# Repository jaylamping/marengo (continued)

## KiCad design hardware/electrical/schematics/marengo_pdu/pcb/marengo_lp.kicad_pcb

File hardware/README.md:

# Hardware

Physical robot design for Marengo: CAD, electrical, prints, and BOM. Mechanics and wiring are defined here first; software reads the exports.

**Status for the software project: [`STATUS.md`](STATUS.md).** Hardware threads update it in the same commit whenever a milestone lands (built/tested parts, joint names, limits, CAN IDs, URDF, new software requirements).

## Layout

| Path | Purpose |
|------|---------|
| [`../cad/`](../cad/) | SolidWorks parts, assemblies, vendor STEP, MCP manifests |
| [`electrical/`](electrical/) | PDB (KiCad stub), harness and CAN documentation |
| [`prints/`](prints/) | STL sources and slicer notes |
| [`bom/`](bom/) | Master BOM and sourcing |
| [`docs/`](docs/) | Kinematics (joint SSOT), torso design, assembly, homing sensors, CAD standards, hardware ADRs, [RobStride manuals](docs/robstride/README.md) |

## Active design

| Target | Status |
|--------|--------|
| Humanoid rev-a (G1/R1-class biped, 1524 mm, 23 DOF) | Torso frame 140×150×340 mm committed; pelvis/shell draft — [`docs/kinematics.md`](docs/kinematics.md) |
| Right arm (5 DOF, live bench) | First subsystem wired and commissioning: [`config/robot.yaml`](../config/robot.yaml) + [`assets/urdf/marengo.urdf`](../assets/urdf/marengo.urdf) (geometry and inertials from CAD, 2026-10-03). It is the first slice of the humanoid arm, not a separate robot |
| Electrical | Pi 5 + 2-CH MCP2515 CAN HAT + BNO085 IMU on the bench. PDB/PDU KiCad project is an empty stub; 48 V pack and full harness are draft |

Full-body runtime templates (not loaded until remaining joints are commissioned): [`config/robot_humanoid.yaml`](../config/robot_humanoid.yaml), [`config/motors_humanoid.yaml`](../config/motors_humanoid.yaml).

## Revision

When you cut a build, record the mechanical/electrical revision here (e.g. `rev-a`, date, known deltas from prior rev).

| Rev | Date | Scope |
|-----|------|-------|
| rev-a (in progress) | 2026 | 2020 upper-torso cage committed; right 5-DOF arm built and on the bench; everything else draft |

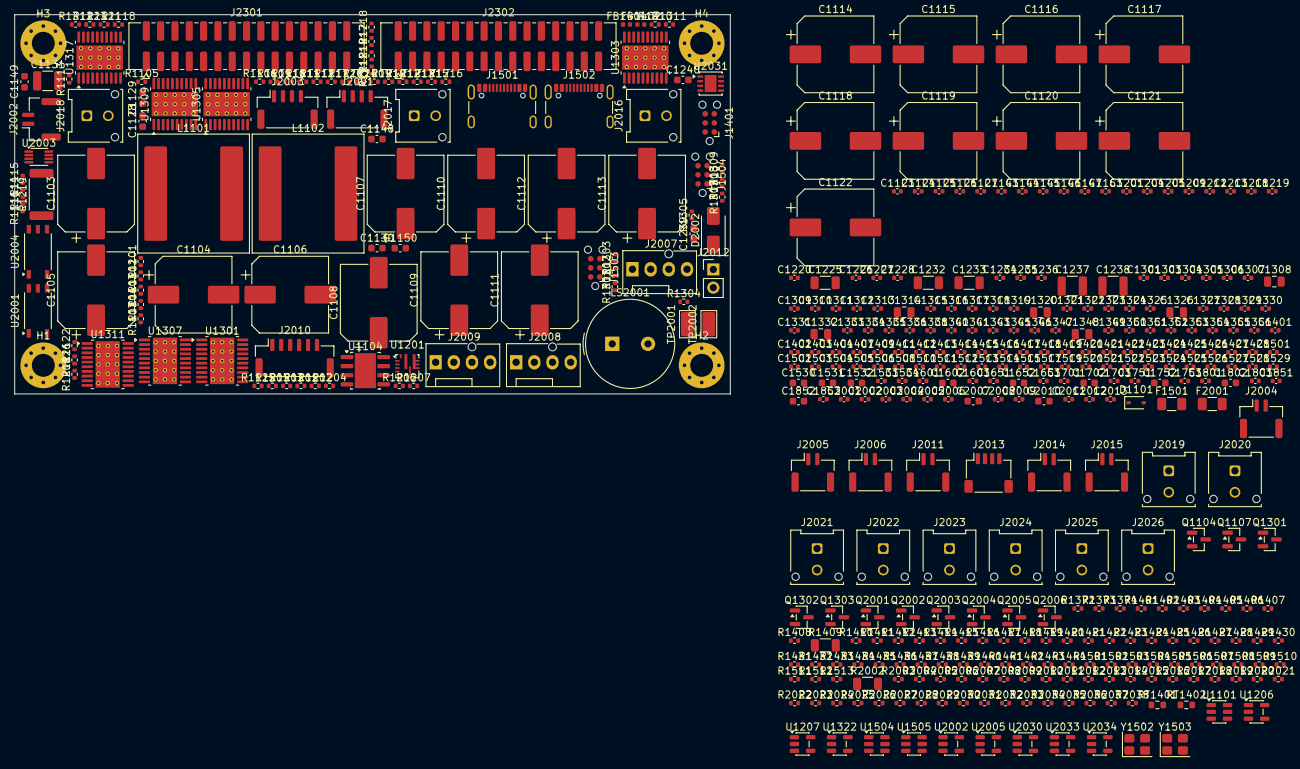
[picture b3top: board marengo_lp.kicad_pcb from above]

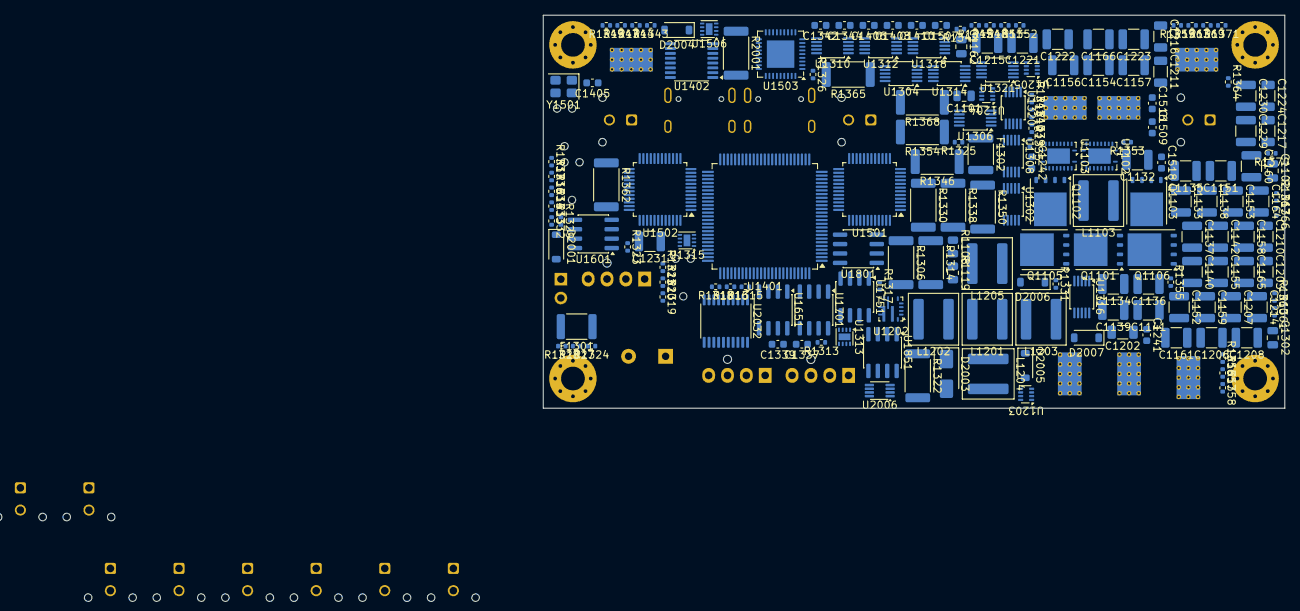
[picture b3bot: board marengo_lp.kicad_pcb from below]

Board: 6 copper layers, 100.0 x 53.0 mm, 611 parts (177 on the bottom side), 354 nets, no tracks yet.

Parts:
C1101, C1102, C1162: 100nF 100V; C_0805_2012Metric
C1103, C1104, C1105, C1106, C1107, C1108, C1109, C1110, C1111, C1112, C1113, C1114, C1115, C1116, C1117, C1118, C1119, C1120, C1121, C1122: 68uF 80V B40950B0686M100; CP_Elec_10x10.5
C1123, C1412, C1413, C1414, C1415, C1416, C1417, C1418, C1419, C1421, C1422, C1423, C1424, C1425, C1426, C1427, C1508, C1517: 10nF; C_0402_1005Metric
C1124: 33pF; C_0402_1005Metric
C1125, C1338, C1343, C1420, C1533: 1nF; C_0402_1005Metric
C1126, C1146, C1220, C1228, C1236: 33nF; C_0402_1005Metric
C1127, C1147: 100nF 25V; C_0402_1005Metric
C1128, C1148: 2.2uF 25V; C_0603_1608Metric
C1129: 18pF C0G 100V; C_0603_1608Metric
C1130, C1150: 100nF 100V; C_0603_1608Metric
C1131, C1132, C1133, C1134, C1135, C1151, C1152, C1153, C1161: 4.7uF 100V; C_1210_3225Metric
C1136, C1137, C1138, C1139, C1140, C1141, C1142, C1164, C1165, C1166, C1206, C1207, C1208, C1214, C1215, C1221, C1222, C1223, C1229, C1230, C1231, C1237, C1238: 22uF 25V; C_1210_3225Metric
C1143: 6.8nF; C_0402_1005Metric
C1144: 10pF; C_0402_1005Metric
C1145: 680pF; C_0402_1005Metric
C1149: 22pF C0G 100V; C_0603_1608Metric
C1154, C1155, C1156, C1157, C1158, C1159, C1160: 10uF 50V; C_1210_3225Metric
C1163, C1204, C1205, C1212, C1213, C1218, C1219, C1226, C1227, C1234, C1235, C1305, C1306, C1311, C1312, C1317, C1318, C1323, C1324, C1329, C1330, C1335, C1336, C1340, C1341, C1345, C1346, C1351, C1352, C1353, C1354, C1355, C1356, C1401, C1402, C1403, C1404, C1407, C1409, C1411, C1428, C1503, C1504, C1505, C1506, C1512, C1513, C1514, C1515, C1521, C1522, C1523, C1524, C1525, C1526, C1527, C1528, C1529, C1534, C1601, C1603, C1651, C1653, C1701, C1703, C1751, C1753, C1801, C1803, C1851, C1853, C2001, C2002, C2003, C2004, C2005, C2006, C2008, C2009, C2011, C2012, C2013: 100nF; C_0402_1005Metric
C1201, C1209: 220pF C0G; C_0402_1005Metric
C1202, C1203, C1210, C1211, C1216, C1217, C1224, C1225, C1232, C1233: 10uF 50V; C_1206_3216Metric
C1239, C1240, C1241, C1242, C1337, C1342, C1531: 1uF 10V; C_0603_1608Metric
C1301: 22nF; C_0402_1005Metric
C1302, C1308, C1314, C1320, C1326, C1332, C1348: 1uF 50V; C_0805_2012Metric
C1303, C1304, C1309, C1310, C1315, C1316, C1321, C1322, C1327, C1328, C1333, C1334, C1349, C1350: 100nF 50V; C_0402_1005Metric
C1307, C1313, C1319, C1325, C1331, C1347: 47nF; C_0402_1005Metric
C1339, C1344, C1532: 10uF 10V; C_0603_1608Metric
C1405, C1406, C1410, C1507, C1516, C1530, C1602, C1652, C1702, C1752, C1802, C1852: 4.7uF; C_0603_1608Metric
C1408, C1509, C1518: 1uF; C_0603_1608Metric
C1501, C1502, C1510, C1511, C1519, C1520: 12pF C0G; C_0402_1005Metric
C2007, C2010: 2.2uF; C_0603_1608Metric
D1101: BAT54 30V; D_SOD-323
D2001, D2007: 1N4148W; D_SOD-123
D2002, D2003: SMAJ15A; D_SMA
D2004, D2005, D2006: BAT54; D_SOD-123
F1301: 2.5A MF-MSMF250/16X-2; Fuse_1812_4532Metric
F1302: 1.1A MF-MSMF110/16-2; Fuse_1812_4532Metric
F1501, F2001: 0.5A polyfuse; Fuse_1206_3216Metric
FB1401, FB1402: BLM15; L_0402_1005Metric
H1, H2, H3, H4: M3 standoff; MountingHole_3.2mm_M3_Pad_Via
J1401, J1503, J1504: SWD Tag-Connect; Tag-Connect_TC2030-IDC-NL_2x03_P1.27mm_Vertical
J1501: USB4105-GF-A, up to Pi; USB_C_Receptacle_GCT_USB4105-xx-A_16P_TopMnt_Horizontal
J1502: USB4105-GF-A, service; USB_C_Receptacle_GCT_USB4105-xx-A_16P_TopMnt_Horizontal
J2001: E-stop loop; JST_GH_SM04B-GHS-TB_1x04-1MP_P1.25mm_Horizontal
J2002: tether, shorting dummy; JST_GH_SM02B-GHS-TB_1x02-1MP_P1.25mm_Horizontal
J2003: wireless contact, shorting plug; JST_GH_SM04B-GHS-TB_1x04-1MP_P1.25mm_Horizontal
J2004: brake thermostat NC; JST_GH_SM02B-GHS-TB_1x02-1MP_P1.25mm_Horizontal
J2005: wireless receiver power; JST_GH_SM02B-GHS-TB_1x02-1MP_P1.25mm_Horizontal
J2006: E-stop reset, NO button; JST_GH_SM02B-GHS-TB_1x02-1MP_P1.25mm_Horizontal
J2007: fan 1; FanPinHeader_1x04_P2.54mm_Vertical
J2008: fan 2; FanPinHeader_1x04_P2.54mm_Vertical
J2009: fan 3; FanPinHeader_1x04_P2.54mm_Vertical
J2010: shell: button + RGB; JST_GH_SM06B-GHS-TB_1x06-1MP_P1.25mm_Horizontal
J2011: charge LED; JST_GH_SM02B-GHS-TB_1x02-1MP_P1.25mm_Horizontal
J2012: bench jumper; PinHeader_1x02_P2.54mm_Vertical
J2013: Qwiic; JST_SH_SM04B-SRSS-TB_1x04-1MP_P1.00mm_Horizontal
J2014: intake NTC; JST_GH_SM02B-GHS-TB_1x02-1MP_P1.25mm_Horizontal
J2015: exhaust NTC; JST_GH_SM02B-GHS-TB_1x02-1MP_P1.25mm_Horizontal
J2016: OUT_24V; Molex_Micro-Fit_3.0_43045-0212_2x01_P3.00mm_Vertical
J2017: OUT_12V_JETSON; Molex_Micro-Fit_3.0_43045-0212_2x01_P3.00mm_Vertical
J2018: OUT_12V_THIRD; Molex_Micro-Fit_3.0_43045-0212_2x01_P3.00mm_Vertical
J2019: OUT_12V_AUX; Molex_Micro-Fit_3.0_43045-0212_2x01_P3.00mm_Vertical
J2020: OUT_12V_PI_STUB; Molex_Micro-Fit_3.0_43045-0212_2x01_P3.00mm_Vertical
J2021: OUT_7V4_SERVO; Molex_Micro-Fit_3.0_43045-0212_2x01_P3.00mm_Vertical
J2022: OUT_5V_PERIPH; Molex_Micro-Fit_3.0_43045-0212_2x01_P3.00mm_Vertical
J2023: OUT_3V3_PERIPH; Molex_Micro-Fit_3.0_43045-0212_2x01_P3.00mm_Vertical
J2024: OUT_SPARE; Molex_Micro-Fit_3.0_43045-0212_2x01_P3.00mm_Vertical
J2025: 5V_CLEAN; Molex_Micro-Fit_3.0_43045-0212_2x01_P3.00mm_Vertical
J2026: 3V3_CLEAN; Molex_Micro-Fit_3.0_43045-0212_2x01_P3.00mm_Vertical
J2301: 2x15 2 mm box, power and logic; Molex_8783230xx_2x15_P2.0mm_Header_Vertical_Polarized
J2302: 2x15 2 mm box, CAN and analog; Molex_8783230xx_2x15_P2.0mm_Header_Vertical_Polarized
L1101: XAL1510-682MED; L_Coilcraft_XAL1510-682
L1102: XAL1510-333MED; L_Coilcraft_XAL1510-333
L1103: XAL6060-223MEC 22uH; L_Coilcraft_XAL6060-XXX
L1201: XAL6060-562MEC 5.6uH; L_Coilcraft_XAL6060-XXX
L1202: XAL6030-332MEC 3.3uH; L_Coilcraft_XAL6030-XXX
L1203: XAL6060-472MEC 4.7uH; L_Coilcraft_XAL6060-XXX
L1204, L1205: XAL6060-682MEC 6.8uH; L_Coilcraft_XAL6060-XXX
LS2001: PS1240P02BT; Buzzer_TDK_PS1240P02BT_D12.2mm_H6.5mm
Q1101: CSD19532Q5B; TDSON-8-1
Q1102, Q1105, Q1106: CSD19534Q5A; TDSON-8-1
Q1103: BSC040N10NS5ATMA1; TDSON-8-1
Q1104, Q1107: BSS123; SOT-23
Q1301, Q1302, Q1303, Q2001, Q2002, Q2003, Q2004, Q2005, Q2006: 2N7002; SOT-23
R1101, R1102, R1112, R1359: 33.2k; R_0402_1005Metric
R1103: 2.37k; R_0402_1005Metric
R1104, R1309, R1317: 6.04k; R_0402_1005Metric
R1105, R1116: 100R; R_0402_1005Metric
R1106, R1117: 2.2R; R_0402_1005Metric
R1107: 348R; R_0402_1005Metric
R1108: 1.21M; R_0805_2012Metric
R1109: 49.9k; R_0402_1005Metric
R1110, R1121, R1203, R1209: 20k; R_0402_1005Metric
R1111, R1122, R1123, R1126, R1206, R1212, R1349, R1353, R1372, R1438, R1439, R1502, R1503, R1507, R1508, R1513, R2005, R2011, R2022, R2023, R2024, R2025, R2026, R2027, R2028, R2029, R2030, R2031, R2038: 100k; R_0402_1005Metric
R1113: 80.6k; R_0402_1005Metric
R1114: 2.8k; R_0402_1005Metric
R1115: 17.8k; R_0402_1005Metric
R1118: 301R; R_0402_1005Metric
R1119: 499k; R_0805_2012Metric
R1120: 18.2k; R_0402_1005Metric
R1124: 43.2k; R_0402_1005Metric
R1125, R1344: 64.9k; R_0402_1005Metric
R1201: 113k; R_0402_1005Metric
R1202, R1208, R1214, R1216, R1218, R1371, R1373, R1374, R1412, R1414, R1416, R1418, R1420, R1422, R1436, R1437, R1440, R1441, R1504, R1505, R1506, R2015, R2017, R2018, R2019, R2020, R2021, R2036, R2037: 10k; R_0402_1005Metric
R1204, R1210: 169k; R_0402_1005Metric
R1205, R1211: 36.1k; R_0402_1005Metric
R1207: 73.2k; R_0402_1005Metric
R1213: 31.6k; R_0402_1005Metric
R1215: 52.3k; R_0402_1005Metric
R1217: 60.4k; R_0402_1005Metric
R1219: 4.7R 1W; R_2512_6332Metric
R1301, R1333, R1357: 4.99k; R_0402_1005Metric
R1302: 475k; R_0402_1005Metric
R1303: 7.87k; R_0402_1005Metric
R1304: 22.1k; R_0402_1005Metric
R1305, R1313, R1321, R1329, R1337, R1345, R1361: 33k; R_0402_1005Metric
R1306, R1314, R1322, R1330, R1338, R1354, R1362, R1365: 10mR 3W; R_2512_6332Metric
R1307, R1308, R1315, R1316, R1323, R1324, R1331, R1332, R1339, R1340, R1347, R1348, R1351, R1352, R1355, R1356, R1363, R1364, R1366, R1367, R1369, R1370: 10R; R_0402_1005Metric
R1310, R1318, R1326, R1334: 442k; R_0402_1005Metric
R1311, R1319, R1327, R1335: 21.5k; R_0402_1005Metric
R1312, R1320, R1328, R1336: 41.2k; R_0402_1005Metric
R1325: 4.53k; R_0402_1005Metric
R1341: 3.01k; R_0402_1005Metric
R1342: 383k; R_0402_1005Metric
R1343: 54.9k; R_0402_1005Metric
R1346, R1350: 5mR 3W; R_2512_6332Metric
R1358: 365k; R_0402_1005Metric
R1360: 97.6k; R_0402_1005Metric
R1368: 2mR 3W; R_2512_6332Metric
R1401, R1402, R1403, R1404, R1405, R1406, R1407, R1408, R1411, R1413, R1415, R1417, R1419, R1421, R1423, R1442, R1443, R1444, R2004, R2006, R2010, R2012, R2016: 1k; R_0402_1005Metric
R1409: 1M 0.1%; R_1206_3216Metric
R1410: 56k 0.1%; R_0402_1005Metric
R1424, R1425, R1426, R1427, R1428, R1429, R1430, R1431, R1432, R1433, R1434, R1435: 2.2k; R_0402_1005Metric
R1501: 12.0k 1%; R_0402_1005Metric
R1509, R1510: 5.1k; R_0402_1005Metric
R1511, R1512: 56k; R_0402_1005Metric
R2001: 680R 1W; R_2512_6332Metric
R2002: 620R 0.25W; R_1206_3216Metric
R2003, R2009: 10k Cat 0 filter; R_0402_1005Metric
R2007, R2013: 160k; R_0402_1005Metric
R2008, R2014: 1M; R_0402_1005Metric
R2032, R2033, R2034, R2035: 330R; R_0402_1005Metric
RT1401, RT1402: 10k B3435; R_0603_1608Metric
TP2001, TP2002: TP; TestPoint_Keystone_5015_Micro_Mini
U1101: LM5050MK-1; TSOT-23-6
U1102, U1103: LM5145RGYR; Texas_RGY_R-PVQFN-N20_EP2.05x3.05mm
U1104: LMR38010SDDAR; SOIC-8-1EP_3.9x4.9mm_P1.27mm_EP2.95x4.9mm_Mask2.71x3.4mm
U1201, U1202: TPS56637RPAR; TPS56637_RPA_VQFN-HR-10
U1203, U1204: TPS62933DRLR; SOT-583-8
U1205: TPS62933FDRLR; SOT-583-8
U1206: TPS7A2050PDBVR; SOT-23-5
U1207: TPS7A2033PDBVR; SOT-23-5
U1301, U1303, U1305, U1307, U1309, U1311, U1317: TPS26631PWPR; HTSSOP-20-1EP_4.4x6.5mm_P0.65mm_EP3.4x6.5mm_Mask2.96x2.96mm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
U1302, U1304, U1306, U1308, U1310, U1312, U1314, U1316, U1318, U1320, U1321: INA238AIDGSR; TSSOP-10_3x3mm_P0.5mm
U1313, U1315, U1506: TPS22965DSGR; Texas_DSG0008A_WSON-8-1EP_2x2mm_P0.5mm_EP0.9x1.6mm
U1322, U2002, U2005, U2030: SN74LVC1G14DBV; SOT-23-5
U1401: STM32G0B1VET6; LQFP-100_14x14mm_P0.5mm
U1402: TCA9546APWR; TSSOP-16_4.4x5mm_P0.65mm
U1501, U1502: STM32G474CET6; LQFP-48_7x7mm_P0.5mm
U1503: USB2514B-I/M2; QFN-36-1EP_6x6mm_P0.5mm_EP3.7x3.7mm
U1504, U1505: USBLC6-2SC6; SOT-23-6
U1601, U1651, U1701, U1751, U1801, U1851: TCAN1462VDRQ1; SOIC-8_3.9x4.9mm_P1.27mm
U2001, U2004: ISOM8710; ISOM8710_DFF
U2003, U2006: SN74LVC1G74DCUR; VSSOP-8_2.3x2mm_P0.5mm
U2031: TPS3431SDRBR; VSON-8-1EP_3x3mm_P0.65mm_EP1.65x2.4mm
U2032: SN74LVC244APWR; TSSOP-20_4.4x6.5mm_P0.65mm
U2033, U2034: SN74LVC1G08DBV; SOT-23-5
Y1501, Y1502, Y1503: ABM8G-24.000MHZ-4Y-T; Crystal_SMD_3225-4Pin_3.2x2.5mm

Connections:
+3V3_AON: C1164.1, C1165.1, C1166.1, C1306.1, C1312.1, C1318.1, C1324.1, C1330.1, C1336.1, C1341.1, C1346.1, C1352.1, C1354.1, C1356.1, C1401.1, C1402.1, C1403.1, C1404.1, C1405.1, C1406.1, C1428.1, C1504.1, C1505.1, C1506.1, C1507.1, C1508.1, C1509.1, C1513.1, C1514.1, C1515.1, C1516.1, C1517.1, C1518.1, C1524.1, C1525.1, C1526.1, C1527.1, C1528.1, C1529.1, C1530.1, C1603.1, C1653.1, C1703.1, C1753.1, C1803.1, C1853.1, C2001.1, C2002.1, C2003.1, C2004.1, C2006.1, C2009.1, C2012.1, C2013.1, FB1401.1, FB1402.1, J1401.1, J1503.1, J1504.1, J2010.1, J2013.2, L1103.2, R1110.2, R1121.2, R1122.1, R1123.1, R1126.2, R1206.2, R1212.2, R1371.2, R1372.2, R1373.2, R1374.2, R1424.2, R1425.2, R1426.2, R1427.2, R1428.2, R1429.2, R1430.2, R1431.2, R1432.2, R1433.2, R1434.2, R1435.2, R1436.2, R1437.2, R1440.2, R1441.2, R1502.2, R1503.2, R1506.2, R2005.2, R2008.2, R2011.2, R2014.2, R2015.2, R2016.2, R2019.2, R2020.2, R2021.2, R2036.2, R2037.2, U1302.6, U1304.2, U1304.6, U1306.6, U1308.6, U1310.1, U1310.6, U1312.6, U1314.2, U1314.6, U1316.6, U1318.6, U1320.1, U1320.6, U1321.1, U1321.2, U1321.6, U1322.5, U1401.11, U1401.13, U1401.64, U1402.16, U1501.1, U1501.20, U1501.21, U1501.24, U1501.36, U1501.48, U1502.1, U1502.20, U1502.21, U1502.24, U1502.36, U1502.48, U1503.5, U1503.10, U1503.15, U1503.23, U1503.29, U1503.36, U1601.5, U1651.5, U1701.5, U1751.5, U1801.5, U1851.5, U2001.5, U2002.5, U2003.7, U2003.8, U2004.5, U2005.5, U2006.7, U2006.8, U2030.5, U2031.1, U2031.5, U2032.20, U2033.5, U2034.5
+3V3_CLEAN: C1242.1, J2026.1, U1207.5
+3V3_HP: C1409.1, C1410.1, FB1402.2, J2301.28
+5V_CLEAN: C1240.1, J2025.1, U1206.5
+12V: C1136.1, C1137.1, C1138.1, C1139.1, C1140.1, C1141.1, C1142.1, C1202.1, C1203.1, C1204.1, C1210.1, C1211.1, C1212.1, C1216.1, C1217.1, C1218.1, C1224.1, C1225.1, C1226.1, C1232.1, C1233.1, C1234.1, C1308.1, C1309.1, C1314.1, C1315.1, C1320.1, C1321.1, C1326.1, C1327.1, D1101.2, F2001.1, J2007.2, J2008.2, J2009.2, R1102.1, R1105.1, R1204.1, R1210.1, R1310.1, R1318.1, R1326.1, R1334.1, R1368.2, R1370.1, R2001.1, U1201.8, U1202.8, U1203.3, U1204.3, U1205.3, U1303.1, U1303.2, U1303.3, U1303.6, U1305.1, U1305.2, U1305.3, U1305.6, U1307.1, U1307.2, U1307.3, U1307.6, U1309.1, U1309.2, U1309.3, U1309.6, U1321.8
+24V: C1154.1, C1155.1, C1156.1, C1157.1, C1158.1, C1159.1, C1160.1, C1302.1, C1303.1, L1102.2, R1113.1, R1116.1, R1302.1, U1301.1, U1301.2, U1301.3, U1301.6
/LP_logic_board/can_bridges_usb_hub/CRFILT: C1521.1, U1503.14
/LP_logic_board/can_bridges_usb_hub/HSE_I_A: C1501.1, U1501.5, Y1501.1
/LP_logic_board/can_bridges_usb_hub/HSE_I_B: C1510.1, U1502.5, Y1502.1
/LP_logic_board/can_bridges_usb_hub/HSE_O_A: C1502.1, U1501.6, Y1501.3
/LP_logic_board/can_bridges_usb_hub/HSE_O_B: C1511.1, U1502.6, Y1502.3
/LP_logic_board/can_bridges_usb_hub/HUB_XI: C1519.1, U1503.33, Y1503.1
/LP_logic_board/can_bridges_usb_hub/HUB_XO: C1520.1, U1503.32, Y1503.3
/LP_logic_board/can_bridges_usb_hub/NRST_A: C1503.1, J1503.3, U1501.7
/LP_logic_board/can_bridges_usb_hub/NRST_B: C1512.1, J1504.3, U1502.7
/LP_logic_board/can_bridges_usb_hub/PLLFILT: C1522.1, U1503.34
/LP_logic_board/can_bridges_usb_hub/RBIAS: R1501.1, U1503.35
/LP_logic_board/can_bridges_usb_hub/STRAP_CF0: R1504.1, U1503.24
/LP_logic_board/can_bridges_usb_hub/STRAP_CF1: R1505.1, U1503.25
/LP_logic_board/can_bridges_usb_hub/STRAP_NR0: R1503.1, U1503.28
/LP_logic_board/can_bridges_usb_hub/STRAP_NR1: R1502.1, U1503.22
/LP_logic_board/can_bridges_usb_hub/SVC_CC1: J1502.A5, R1511.2
/LP_logic_board/can_bridges_usb_hub/SVC_CC2: J1502.B5, R1512.2
/LP_logic_board/can_bridges_usb_hub/SVC_CT: C1533.1, U1506.6
/LP_logic_board/can_bridges_usb_hub/SVC_PWR_EN: R1513.1, U1503.20, U1506.3
/LP_logic_board/can_bridges_usb_hub/SVC_SW: C1532.1, F1501.1, U1506.7, U1506.8
/LP_logic_board/can_bridges_usb_hub/SVC_VBUS: F1501.2, J1502.A4, J1502.A9, J1502.B4, J1502.B9, U1505.5
/LP_logic_board/can_bridges_usb_hub/SWCLK_A: J1503.4, U1501.38
/LP_logic_board/can_bridges_usb_hub/SWCLK_B: J1504.4, U1502.38
/LP_logic_board/can_bridges_usb_hub/SWDIO_A: J1503.2, U1501.37
/LP_logic_board/can_bridges_usb_hub/SWDIO_B: J1504.2, U1502.37
/LP_logic_board/can_bridges_usb_hub/UP_CC1: J1501.A5, R1509.1
/LP_logic_board/can_bridges_usb_hub/UP_CC2: J1501.B5, R1510.1
/LP_logic_board/can_bridges_usb_hub/UP_VBUS: C1534.1, J1501.A4, J1501.A9, J1501.B4, J1501.B9, R1507.1, U1504.5
/LP_logic_board/can_bridges_usb_hub/USB_SVC_DM: J1502.A7, J1502.B7, U1503.8, U1505.1, U1505.6
/LP_logic_board/can_bridges_usb_hub/USB_SVC_DP: J1502.A6, J1502.B6, U1503.9, U1505.3, U1505.4
/LP_logic_board/can_bridges_usb_hub/USB_UP_DM: J1501.A7, J1501.B7, U1503.30, U1504.1, U1504.6
/LP_logic_board/can_bridges_usb_hub/USB_UP_DP: J1501.A6, J1501.B6, U1503.31, U1504.3, U1504.4
/LP_logic_board/can_bridges_usb_hub/VBUS_DET: R1507.2, R1508.1, U1503.27
/LP_logic_board/front_end_12v_24v/BOOT_AON: C1163.1, U1104.7
/LP_logic_board/front_end_12v_24v/BST_12: C1127.1, U1102.17
/LP_logic_board/front_end_12v_24v/BST_24: C1147.1, U1103.17
/LP_logic_board/front_end_12v_24v/BSW_12: C1127.2, R1106.1
/LP_logic_board/front_end_12v_24v/BSW_24: C1147.2, R1117.1
/LP_logic_board/front_end_12v_24v/CC_12: C1123.1, R1104.2
/LP_logic_board/front_end_12v_24v/CC_24: C1143.1, R1115.2
/LP_logic_board/front_end_12v_24v/COMP_12: C1124.1, R1104.1, U1102.4
/LP_logic_board/front_end_12v_24v/COMP_24: C1144.1, R1115.1, U1103.4
/LP_logic_board/front_end_12v_24v/EN_12: Q1104.3, R1108.2, R1109.1, U1102.1
/LP_logic_board/front_end_12v_24v/EN_24: Q1107.3, R1119.2, R1120.1, U1103.1
/LP_logic_board/front_end_12v_24v/FB_12: C1123.2, C1124.2, C1125.2, R1102.2, R1103.1, U1102.5
/LP_logic_board/front_end_12v_24v/FB_24: C1143.2, C1144.2, C1145.2, R1113.2, R1114.1, U1103.5
/LP_logic_board/front_end_12v_24v/FB_AON: R1123.2, R1124.1, U1104.5
/LP_logic_board/front_end_12v_24v/FF_12: C1125.1, R1105.2
/LP_logic_board/front_end_12v_24v/FF_24: C1145.1, R1116.2
/LP_logic_board/front_end_12v_24v/HO_12: Q1102.4, U1102.18
/LP_logic_board/front_end_12v_24v/HO_24: Q1105.4, U1103.18
/LP_logic_board/front_end_12v_24v/ILIM_12: C1129.1, R1107.1, U1102.11
/LP_logic_board/front_end_12v_24v/ILIM_24: C1149.1, R1118.1, U1103.11
/LP_logic_board/front_end_12v_24v/LO_12: Q1103.4, U1102.13
/LP_logic_board/front_end_12v_24v/LO_24: Q1106.4, U1103.13
/LP_logic_board/front_end_12v_24v/OR_GATE: Q1101.4, U1101.5
/LP_logic_board/front_end_12v_24v/PG_AON: R1126.1, U1104.6
/LP_logic_board/front_end_12v_24v/RT_12: R1101.1, U1102.2
/LP_logic_board/front_end_12v_24v/RT_24: R1112.1, U1103.2
/LP_logic_board/front_end_12v_24v/RT_AON: R1125.1, U1104.4
/LP_logic_board/front_end_12v_24v/SS_12: C1126.1, U1102.3
/LP_logic_board/front_end_12v_24v/SS_24: C1146.1, U1103.3
/LP_logic_board/front_end_12v_24v/SW12: L1101.1, Q1102.1, Q1102.2, Q1102.3, Q1103.5, R1106.2, R1107.2, U1102.19
/LP_logic_board/front_end_12v_24v/SW24: L1102.1, Q1105.1, Q1105.2, Q1105.3, Q1106.5, R1117.2, R1118.2, U1103.19
/LP_logic_board/front_end_12v_24v/SW_AON: C1163.2, L1103.1, U1104.8
/LP_logic_board/front_end_12v_24v/SYNC_24: U1102.7, U1103.8
/LP_logic_board/front_end_12v_24v/VCC_12: C1128.1, D1101.1, U1102.8, U1102.14
/LP_logic_board/front_end_12v_24v/VCC_24: C1148.1, U1103.14
/LP_logic_board/front_end_12v_24v/VSYS_OR: C1102.1, C1103.1, C1104.1, C1105.1, C1106.1, C1107.1, C1108.1, C1109.1, C1110.1, C1111.1, C1112.1, C1113.1, C1114.1, C1115.1, C1116.1, C1117.1, C1118.1, C1119.1, C1120.1, C1121.1, C1122.1, C1130.1, C1131.1, C1132.1, C1133.1, C1134.1, C1135.1, C1161.1, C1162.1, Q1101.5, Q1102.5, R1108.1, U1101.6, U1102.20, U1104.2, U1104.3
/LP_logic_board/io_fans_estop_loop/ARM_A: R2004.1, R2017.1, U2003.5
/LP_logic_board/io_fans_estop_loop/ARM_B: R2010.1, U2006.5
/LP_logic_board/io_fans_estop_loop/BUZ_D: D2007.2, LS2001.2, Q2006.3
/LP_logic_board/io_fans_estop_loop/CLR_A: U2003.6, U2033.4
/LP_logic_board/io_fans_estop_loop/CLR_B: U2006.6, U2034.4
/LP_logic_board/io_fans_estop_loop/ESTOP_RST: U2003.1, U2006.1, U2030.4
/LP_logic_board/io_fans_estop_loop/ESTOP_RST_N: C2011.1, J2006.1, R2015.1, U2030.2
/LP_logic_board/io_fans_estop_loop/FAN1_DRV: J2007.4, Q2003.3
/LP_logic_board/io_fans_estop_loop/FAN2_DRV: J2008.4, Q2004.3
/LP_logic_board/io_fans_estop_loop/FAN3_DRV: J2009.4, Q2005.3
/LP_logic_board/io_fans_estop_loop/INV_A: C2005.1, C2007.1, D2004.2, R2003.2, R2007.2, R2008.1, U2002.2
/LP_logic_board/io_fans_estop_loop/INV_B: C2008.1, C2010.1, D2005.2, R2009.2, R2013.2, R2014.1, U2005.2
/LP_logic_board/io_fans_estop_loop/LB: J2010.4, R2034.2
/LP_logic_board/io_fans_estop_loop/LC: J2011.1, R2035.2
/LP_logic_board/io_fans_estop_loop/LG: J2010.3, R2033.2
/LP_logic_board/io_fans_estop_loop/LOOP_M: U2001.2, U2004.1
/LP_logic_board/io_fans_estop_loop/LOOP_N: D2001.2, R2002.1, U2004.2
/LP_logic_board/io_fans_estop_loop/LOOP_OUT: D2002.1, J2001.1, R2001.2, TP2001.1
/LP_logic_board/io_fans_estop_loop/LOOP_RET: D2001.1, D2003.1, J2004.2, TP2002.1, U2001.1
/LP_logic_board/io_fans_estop_loop/LOOP_TH: J2003.3, J2004.1
/LP_logic_board/io_fans_estop_loop/LR: J2010.2, R2032.2
/LP_logic_board/io_fans_estop_loop/OPTO_A: D2004.1, R2003.1, R2006.1, R2007.1, U2001.4
/LP_logic_board/io_fans_estop_loop/OPTO_B: D2005.1, R2009.1, R2012.1, R2013.1, U2004.4
/LP_logic_board/io_fans_estop_loop/OUT_A: U2002.4, U2003.2, U2033.1
/LP_logic_board/io_fans_estop_loop/OUT_B: U2005.4, U2006.2, U2034.1
/LP_logic_board/io_fans_estop_loop/PORT_OE_N: U2003.3, U2032.1, U2032.19
/LP_logic_board/io_fans_estop_loop/TETH_A: J2001.3, J2002.1
/LP_logic_board/io_fans_estop_loop/TETH_B: J2002.2, J2003.1
/LP_logic_board/io_fans_estop_loop/WL_12V: F2001.2, J2005.1
/LP_logic_board/pol_rails/BOOT_5V: C1213.1, U1202.7
/LP_logic_board/pol_rails/BOOT_7V4: C1205.1, U1201.7
/LP_logic_board/pol_rails/BST_3V3: C1219.1, U1203.6
/LP_logic_board/pol_rails/BST_5V6: C1235.1, U1205.6
/LP_logic_board/pol_rails/BST_SPARE: C1227.1, U1204.6
/LP_logic_board/pol_rails/ENB_5V: R1210.2, R1211.1, U1202.1
/LP_logic_board/pol_rails/ENB_7V4: R1204.2, R1205.1, U1201.1
/LP_logic_board/pol_rails/FB_3V3: R1213.2, R1214.1, U1203.8
/LP_logic_board/pol_rails/FB_5V: C1209.2, R1207.2, R1208.1, U1202.2
/LP_logic_board/pol_rails/FB_5V6: R1217.2, R1218.1, U1205.8
/LP_logic_board/pol_rails/FB_7V4: C1201.2, R1201.2, R1202.1, U1201.2
/LP_logic_board/pol_rails/FB_SPARE: R1215.2, R1216.1, U1204.8
/LP_logic_board/pol_rails/FF_5V: C1209.1, R1209.2
/LP_logic_board/pol_rails/FF_7V4: C1201.1, R1203.2
/LP_logic_board/pol_rails/IN_CLEAN3: C1241.1, R1219.2, U1207.1
/LP_logic_board/pol_rails/PG_5V: R1212.1, U1202.4
/LP_logic_board/pol_rails/PG_7V4: R1206.1, U1201.4
/LP_logic_board/pol_rails/SS_3V3: C1220.1, U1203.7
/LP_logic_board/pol_rails/SS_5V6: C1236.1, U1205.7
/LP_logic_board/pol_rails/SS_SPARE: C1228.1, U1204.7
/LP_logic_board/pol_rails/SW_3V3: C1219.2, L1203.1, U1203.5
/LP_logic_board/pol_rails/SW_5V: C1213.2, L1202.1, U1202.6
/LP_logic_board/pol_rails/SW_5V6: C1235.2, L1205.1, U1205.5
/LP_logic_board/pol_rails/SW_7V4: C1205.2, L1201.1, U1201.6
/LP_logic_board/pol_rails/SW_SPARE: C1227.2, L1204.1, U1204.5
/LP_logic_board/rail_switches_meters/CT_3V3: C1343.1, U1315.6
/LP_logic_board/rail_switches_meters/CT_5V: C1338.1, U1313.6
/LP_logic_board/rail_switches_meters/DV_7V4: C1331.1, U1311.10
/LP_logic_board/rail_switches_meters/DV_12V_AUX: C1319.1, U1307.10
/LP_logic_board/rail_switches_meters/DV_12V_JETSON: C1307.1, U1303.10
/LP_logic_board/rail_switches_meters/DV_12V_PI: C1325.1, U1309.10
/LP_logic_board/rail_switches_meters/DV_12V_THIRD: C1313.1, U1305.10
/LP_logic_board/rail_switches_meters/DV_24V: C1301.1, U1301.10
/LP_logic_board/rail_switches_meters/DV_SPARE: C1347.1, U1317.10
/LP_logic_board/rail_switches_meters/IL_7V4: R1341.1, U1311.11
/LP_logic_board/rail_switches_meters/IL_12V_AUX: R1325.1, U1307.11
/LP_logic_board/rail_switches_meters/IL_12V_JETSON: R1309.1, U1303.11
/LP_logic_board/rail_switches_meters/IL_12V_PI: R1333.1, U1309.11
/LP_logic_board/rail_switches_meters/IL_12V_THIRD: R1317.1, U1305.11
/LP_logic_board/rail_switches_meters/IL_24V: R1301.1, U1301.11
/LP_logic_board/rail_switches_meters/IL_SPARE: R1357.1, U1317.11
/LP_logic_board/rail_switches_meters/OV_7V4: R1343.2, R1344.1, U1311.8
/LP_logic_board/rail_switches_meters/OV_12V_AUX: R1327.2, R1328.1, U1307.8
/LP_logic_board/rail_switches_meters/OV_12V_JETSON: R1311.2, R1312.1, U1303.8
/LP_logic_board/rail_switches_meters/OV_12V_PI: R1335.2, R1336.1, U1309.8
/LP_logic_board/rail_switches_meters/OV_12V_THIRD: R1319.2, R1320.1, U1305.8
/LP_logic_board/rail_switches_meters/OV_24V: R1303.2, R1304.1, U1301.8
/LP_logic_board/rail_switches_meters/OV_SPARE: R1359.2, R1360.1, U1317.8
/LP_logic_board/rail_switches_meters/RAW_5V6_M: R1365.2, R1367.1, U1320.8
/LP_logic_board/rail_switches_meters/SHED_12V: Q1301.1, Q1302.1, Q1303.1, U1322.4
/LP_logic_board/rail_switches_meters/SHED_N: R1371.1, U1321.3, U1322.2
/LP_logic_board/rail_switches_meters/SN_3V3: C1345.2, R1356.2, U1316.9
/LP_logic_board/rail_switches_meters/SN_5V: C1340.2, R1352.2, U1314.9
/LP_logic_board/rail_switches_meters/SN_7V4: C1335.2, R1348.2, U1312.9
/LP_logic_board/rail_switches_meters/SN_12V_AUX: C1323.2, R1332.2, U1308.9
/LP_logic_board/rail_switches_meters/SN_12V_JETSON: C1311.2, R1316.2, U1304.9
/LP_logic_board/rail_switches_meters/SN_12V_PI: C1329.2, R1340.2, U1310.9
/LP_logic_board/rail_switches_meters/SN_12V_THIRD: C1317.2, R1324.2, U1306.9
/LP_logic_board/rail_switches_meters/SN_24V: C1305.2, R1308.2, U1302.9
/LP_logic_board/rail_switches_meters/SN_CLEAN: C1353.2, R1367.2, U1320.9
/LP_logic_board/rail_switches_meters/SN_SPARE: C1351.2, R1364.2, U1318.9
/LP_logic_board/rail_switches_meters/SN_T12: C1355.2, R1370.2, U1321.9
/LP_logic_board/rail_switches_meters/SP_3V3: C1345.1, R1355.2, U1316.10
/LP_logic_board/rail_switches_meters/SP_5V: C1340.1, R1351.2, U1314.10
/LP_logic_board/rail_switches_meters/SP_7V4: C1335.1, R1347.2, U1312.10
/LP_logic_board/rail_switches_meters/SP_12V_AUX: C1323.1, R1331.2, U1308.10
/LP_logic_board/rail_switches_meters/SP_12V_JETSON: C1311.1, R1315.2, U1304.10
/LP_logic_board/rail_switches_meters/SP_12V_PI: C1329.1, R1339.2, U1310.10
/LP_logic_board/rail_switches_meters/SP_12V_THIRD: C1317.1, R1323.2, U1306.10
/LP_logic_board/rail_switches_meters/SP_24V: C1305.1, R1307.2, U1302.10
/LP_logic_board/rail_switches_meters/SP_CLEAN: C1353.1, R1366.2, U1320.10
/LP_logic_board/rail_switches_meters/SP_SPARE: C1351.1, R1363.2, U1318.10
/LP_logic_board/rail_switches_meters/SP_T12: C1355.1, R1369.2, U1321.10
/LP_logic_board/rail_switches_meters/SW_3V3: C1344.1, F1302.1, U1315.7, U1315.8
/LP_logic_board/rail_switches_meters/SW_3V3_PF: F1302.2, R1354.1, R1355.1
/LP_logic_board/rail_switches_meters/SW_5V: C1339.1, F1301.1, U1313.7, U1313.8
/LP_logic_board/rail_switches_meters/SW_5V_PF: F1301.2, R1350.1, R1351.1
/LP_logic_board/rail_switches_meters/SW_7V4: C1334.1, R1346.1, R1347.1, U1311.18, U1311.19, U1311.20
/LP_logic_board/rail_switches_meters/SW_12V_AUX: C1322.1, R1330.1, R1331.1, U1307.18, U1307.19, U1307.20
/LP_logic_board/rail_switches_meters/SW_12V_JETSON: C1310.1, R1314.1, R1315.1, U1303.18, U1303.19, U1303.20
/LP_logic_board/rail_switches_meters/SW_12V_PI: C1328.1, R1338.1, R1339.1, U1309.18, U1309.19, U1309.20
/LP_logic_board/rail_switches_meters/SW_12V_THIRD: C1316.1, R1322.1, R1323.1, U1305.18, U1305.19, U1305.20
/LP_logic_board/rail_switches_meters/SW_24V: C1304.1, R1306.1, R1307.1, U1301.18, U1301.19, U1301.20
/LP_logic_board/rail_switches_meters/SW_SPARE: C1350.1, R1362.1, R1363.1, U1317.18, U1317.19, U1317.20
/LP_logic_board/rail_switches_meters/UV_7V4: R1342.2, R1343.1, U1311.7
/LP_logic_board/rail_switches_meters/UV_12V_AUX: R1326.2, R1327.1, U1307.7
/LP_logic_board/rail_switches_meters/UV_12V_JETSON: R1310.2, R1311.1, U1303.7
/LP_logic_board/rail_switches_meters/UV_12V_PI: R1334.2, R1335.1, U1309.7
/LP_logic_board/rail_switches_meters/UV_12V_THIRD: R1318.2, R1319.1, U1305.7
/LP_logic_board/rail_switches_meters/UV_24V: R1302.2, R1303.1, U1301.7
/LP_logic_board/rail_switches_meters/UV_SPARE: R1358.2, R1359.1, U1317.7
/LP_logic_board/supervisor_mcu/+3V3_A: C1407.1, C1408.1, FB1401.2, R1412.1, R1414.1, R1416.1, R1418.1, R1420.1, R1422.1, U1401.12
/LP_logic_board/supervisor_mcu/ADC_IM1: C1412.1, R1401.2, U1401.25
/LP_logic_board/supervisor_mcu/ADC_IM2: C1413.1, R1402.2, U1401.26
/LP_logic_board/supervisor_mcu/ADC_IM3: C1414.1, R1403.2, U1401.27
/LP_logic_board/supervisor_mcu/ADC_IM4: C1415.1, R1404.2, U1401.28
/LP_logic_board/supervisor_mcu/ADC_IM5: C1416.1, R1405.2, U1401.29
/LP_logic_board/supervisor_mcu/ADC_IM6: C1417.1, R1406.2, U1401.30
/LP_logic_board/supervisor_mcu/ADC_MID: C1418.1, R1407.2, U1401.33
/LP_logic_board/supervisor_mcu/ADC_NTC1: C1422.1, R1413.2, U1401.35
/LP_logic_board/supervisor_mcu/ADC_NTC2: C1423.1, R1415.2, U1401.36
/LP_logic_board/supervisor_mcu/ADC_NTC3: C1424.1, R1417.2, U1401.37
/LP_logic_board/supervisor_mcu/ADC_NTCB: C1425.1, R1419.2, U1401.49
/LP_logic_board/supervisor_mcu/ADC_NTCE: C1427.1, R1423.2, U1401.51
/LP_logic_board/supervisor_mcu/ADC_NTCI: C1426.1, R1421.2, U1401.50
/LP_logic_board/supervisor_mcu/ADC_VMOT: C1419.1, R1408.2, U1401.32
/LP_logic_board/supervisor_mcu/ADC_VSYS: C1421.1, R1411.2, U1401.31
/LP_logic_board/supervisor_mcu/I2C_MUX_SCL: R1429.1, U1401.21, U1402.14
/LP_logic_board/supervisor_mcu/I2C_MUX_SDA: R1428.1, U1401.22, U1402.15
/LP_logic_board/supervisor_mcu/NTC_B2: R1414.2, R1415.1, RT1401.1
/LP_logic_board/supervisor_mcu/NTC_B3: R1416.2, R1417.1, RT1402.1
/LP_logic_board/supervisor_mcu/SUP_NRST: C1411.1, J1401.3, U1401.17
/LP_logic_board/supervisor_mcu/SUP_SWCLK: J1401.4, U1401.74
/LP_logic_board/supervisor_mcu/SUP_SWDIO: J1401.2, U1401.73
/LP_logic_board/supervisor_mcu/TCA_RST_N: R1437.1, U1401.90, U1402.3
/LP_logic_board/supervisor_mcu/VSYS_DIV: C1420.1, R1409.2, R1410.1, R1411.1
AFE_ALERT: J2301.23, R1436.1, U1401.93
AFE_DFETOFF_SUP: J2301.24, U1401.92
AFE_RST_SHUT: J2301.25, U1401.91
BANK_B_CLOSE: J2301.14, U1401.87
BENCH_JUMPER: J2012.1, R2037.1, U1401.88
BUCK12_OFF: Q1104.1, R1111.2, U1401.23
BUCK24_OFF: Q1107.1, R1122.2, U1401.24
BUZZER: Q2006.1, R2038.1, U1401.79
CAN1_H: J2302.1, U1601.7
CAN1_L: J2302.2, U1601.6
CAN1_RXD: U1501.45, U1601.4
CAN1_TXD: U1501.46, U1601.1
CAN2_H: J2302.4, U1651.7
CAN2_L: J2302.5, U1651.6
CAN2_RXD: U1501.26, U1651.4
CAN2_TXD: U1501.27, U1651.1
CAN3_H: J2302.7, U1701.7
CAN3_L: J2302.8, U1701.6
CAN3_RXD: U1501.30, U1701.4
CAN3_TXD: U1501.39, U1701.1
CAN4_H: J2302.10, U1751.7
CAN4_L: J2302.11, U1751.6
CAN4_RXD: U1502.45, U1751.4
CAN4_TXD: U1502.46, U1751.1
CAN5_H: J2302.13, U1801.7
CAN5_L: J2302.14, U1801.6
CAN5_RXD: U1502.26, U1801.4
CAN5_TXD: U1502.27, U1801.1
CAN6_H: J2302.16, U1851.7
CAN6_L: J2302.17, U1851.6
CAN6_RXD: U1502.30, U1851.4
CAN6_TXD: U1502.39, U1851.1
CHARGER_PRESENT: J2301.30, U1401.86
CHARGE_LED: R2035.1, U1401.78
CLAMP_STATUS: J2301.29, U1401.85
EN_3V3: R1353.1, U1315.3, U1401.43
EN_5V: R1349.1, U1313.3, U1401.41
EN_7V4: R1345.1, U1311.13, U1401.40
EN_12V_AUX: Q1302.3, R1329.1, R1443.2, U1307.13
EN_12V_AUX_M: R1443.1, U1401.5
EN_12V_JETSON: R1313.1, U1303.13, U1401.97
EN_12V_PI: R1337.1, U1309.13, U1401.6
EN_12V_THIRD: Q1301.3, R1321.1, R1442.2, U1305.13
EN_12V_THIRD_M: R1442.1, U1401.4
EN_24V: R1305.1, U1301.13, U1401.96
EN_CLEAN3: R1439.1, U1207.3, U1401.1
EN_CLEAN5: R1438.1, U1206.3, U1401.47
EN_SPARE: Q1303.3, R1361.1, R1444.2, U1317.13
EN_SPARE_M: R1444.1, U1401.45
ESTOP_ARMED: R2017.2, U1401.94
ESTOP_EN_A: J2301.10, Q2001.3, R2004.2
ESTOP_EN_B: J2301.11, Q2002.3, R2010.2
FAN1_PWM: Q2003.1, R2022.1, U1401.42
FAN1_TACH: J2007.3, R2019.1, U1401.65
FAN2_PWM: Q2004.1, R2023.1, U1401.44
FAN2_TACH: J2008.3, R2020.1, U1401.66
FAN3_PWM: Q2005.1, R2024.1, U1401.46
FAN3_TACH: J2009.3, R2021.1, U1401.67
FLT_A: J2302.3, U1401.48
GND: C1101.2, C1102.2, C1103.2, C1104.2, C1105.2, C1106.2, C1107.2, C1108.2, C1109.2, C1110.2, C1111.2, C1112.2, C1113.2, C1114.2, C1115.2, C1116.2, C1117.2, C1118.2, C1119.2, C1120.2, C1121.2, C1122.2, C1126.2, C1128.2, C1129.2, C1130.2, C1131.2, C1132.2, C1133.2, C1134.2, C1135.2, C1136.2, C1137.2, C1138.2, C1139.2, C1140.2, C1141.2, C1142.2, C1146.2, C1148.2, C1149.2, C1150.2, C1151.2, C1152.2, C1153.2, C1154.2, C1155.2, C1156.2, C1157.2, C1158.2, C1159.2, C1160.2, C1161.2, C1162.2, C1164.2, C1165.2, C1166.2, C1202.2, C1203.2, C1204.2, C1206.2, C1207.2, C1208.2, C1210.2, C1211.2, C1212.2, C1214.2, C1215.2, C1216.2, C1217.2, C1218.2, C1220.2, C1221.2, C1222.2, C1223.2, C1224.2, C1225.2, C1226.2, C1228.2, C1229.2, C1230.2, C1231.2, C1232.2, C1233.2, C1234.2, C1236.2, C1237.2, C1238.2, C1239.2, C1240.2, C1241.2, C1242.2, C1301.2, C1302.2, C1303.2, C1304.2, C1306.2, C1307.2, C1308.2, C1309.2, C1310.2, C1312.2, C1313.2, C1314.2, C1315.2, C1316.2, C1318.2, C1319.2, C1320.2, C1321.2, C1322.2, C1324.2, C1325.2, C1326.2, C1327.2, C1328.2, C1330.2, C1331.2, C1332.2, C1333.2, C1334.2, C1336.2, C1337.2, C1338.2, C1339.2, C1341.2, C1342.2, C1343.2, C1344.2, C1346.2, C1347.2, C1348.2, C1349.2, C1350.2, C1352.2, C1354.2, C1356.2, C1401.2, C1402.2, C1403.2, C1404.2, C1405.2, C1406.2, C1407.2, C1408.2, C1409.2, C1410.2, C1411.2, C1412.2, C1413.2, C1414.2, C1415.2, C1416.2, C1417.2, C1418.2, C1419.2, C1420.2, C1421.2, C1422.2, C1423.2, C1424.2, C1425.2, C1426.2, C1427.2, C1428.2, C1501.2, C1502.2, C1503.2, C1504.2, C1505.2, C1506.2, C1507.2, C1508.2, C1509.2, C1510.2, C1511.2, C1512.2, C1513.2, C1514.2, C1515.2, C1516.2, C1517.2, C1518.2, C1519.2, C1520.2, C1521.2, C1522.2, C1523.2, C1524.2, C1525.2, C1526.2, C1527.2, C1528.2, C1529.2, C1530.2, C1531.2, C1532.2, C1533.2, C1534.2, C1601.2, C1602.2, C1603.2, C1651.2, C1652.2, C1653.2, C1701.2, C1702.2, C1703.2, C1751.2, C1752.2, C1753.2, C1801.2, C1802.2, C1803.2, C1851.2, C1852.2, C1853.2, C2001.2, C2002.2, C2003.2, C2004.2, C2005.2, C2006.2, C2007.2, C2008.2, C2009.2, C2010.2, C2011.2, C2012.2, C2013.2, D2002.2, D2003.2, J1401.5, J1501.A1, J1501.A12, J1501.B1, J1501.B12, J1501.SH, J1502.A1, J1502.A12, J1502.B1, J1502.B12, J1502.SH, J1503.5, J1504.5, J2001.2, J2001.4, J2003.2, J2003.4, J2005.2, J2006.2, J2007.1, J2008.1, J2009.1, J2010.6, J2011.2, J2012.2, J2013.1, J2014.2, J2015.2, J2016.2, J2017.2, J2018.2, J2019.2, J2020.2, J2021.2, J2022.2, J2023.2, J2024.2, J2025.2, J2026.2, J2301.7, J2301.8, J2301.9, J2301.12, J2302.6, J2302.9, J2302.12, J2302.15, J2302.18, J2302.19, J2302.30, Q1103.1, Q1103.2, Q1103.3, Q1104.2, Q1106.1, Q1106.2, Q1106.3, Q1107.2, Q1301.2, Q1302.2, Q1303.2, Q2001.2, Q2002.2, Q2003.2, Q2004.2, Q2005.2, Q2006.2, R1101.2, R1103.2, R1109.2, R1111.1, R1112.2, R1114.2, R1120.2, R1124.2, R1125.2, R1202.2, R1205.2, R1208.2, R1211.2, R1214.2, R1216.2, R1218.2, R1301.2, R1304.2, R1305.2, R1309.2, R1312.2, R1313.2, R1317.2, R1320.2, R1321.2, R1325.2, R1328.2, R1329.2, R1333.2, R1336.2, R1337.2, R1341.2, R1344.2, R1345.2, R1349.2, R1353.2, R1357.2, R1360.2, R1361.2, R1410.2, R1438.2, R1439.2, R1501.2, R1504.2, R1505.2, R1508.2, R1509.2, R1510.2, R1513.2, R2002.2, R2022.2, R2023.2, R2024.2, R2025.2, R2026.2, R2027.2, R2028.2, R2029.2, R2030.2, R2031.2, R2038.2, RT1401.2, RT1402.2, U1101.2, U1101.3, U1102.6, U1102.12, U1102.15, U1102.21, U1103.6, U1103.12, U1103.15, U1103.21, U1104.1, U1104.9, U1201.3, U1201.9, U1202.3, U1202.9, U1203.4, U1204.4, U1205.4, U1206.2, U1207.2, U1301.9, U1301.16, U1301.21, U1302.1, U1302.2, U1302.7, U1303.9, U1303.16, U1303.21, U1304.1, U1304.7, U1305.9, U1305.16, U1305.21, U1306.1, U1306.7, U1307.9, U1307.16, U1307.21, U1308.1, U1308.7, U1309.9, U1309.16, U1309.21, U1310.2, U1310.7, U1311.9, U1311.16, U1311.21, U1312.1, U1312.2, U1312.7, U1313.5, U1313.9, U1314.1, U1314.7, U1315.5, U1315.9, U1316.1, U1316.7, U1317.9, U1317.16, U1317.21, U1318.1, U1318.7, U1320.2, U1320.7, U1321.7, U1322.3, U1401.14, U1401.63, U1402.1, U1402.2, U1402.8, U1402.13, U1501.19, U1501.23, U1501.35, U1501.47, U1502.19, U1502.23, U1502.35, U1502.47, U1503.11, U1503.37, U1504.2, U1505.2, U1506.5, U1506.9, U1601.2, U1601.8, U1651.2, U1651.8, U1701.2, U1701.8, U1751.2, U1751.8, U1801.2, U1801.8, U1851.2, U1851.8, U2001.3, U2002.3, U2003.4, U2004.3, U2005.3, U2006.4, U2030.3, U2031.4, U2031.9, U2032.10, U2032.15, U2032.17, U2033.3, U2034.3, Y1501.2, Y1501.4, Y1502.2, Y1502.4, Y1503.2, Y1503.4
HUB_RST_N: C1523.1, R1506.1, U1401.89, U1503.26
I2C_AFE_SCL: J2301.22, R1427.1, U1401.52
I2C_AFE_SDA: J2301.21, R1426.1, U1401.53
I2C_A_SCL: R1431.1, U1302.5, U1304.5, U1306.5, U1308.2, U1308.5, U1310.5, U1321.5, U1402.5
I2C_A_SDA: R1430.1, U1302.4, U1304.4, U1306.2, U1306.4, U1308.4, U1310.4, U1321.4, U1402.4
I2C_B_SCL: R1433.1, U1312.5, U1314.5, U1316.5, U1318.2, U1318.5, U1320.5, U1402.7
I2C_B_SDA: R1432.1, U1312.4, U1314.4, U1316.2, U1316.4, U1318.4, U1320.4, U1402.6
I2C_HP_SCL: J2301.27, R1425.1, U1401.98
I2C_HP_SDA: J2301.26, R1424.1, U1401.99
IMON1: J2302.20, R1401.1
IMON2: J2302.21, R1402.1
IMON3: J2302.22, R1403.1
IMON4: J2302.23, R1404.1
IMON5: J2302.24, R1405.1
IMON6: J2302.25, R1406.1
L12_OUT: L1101.2, R1368.1, R1369.1
LED_B: R2034.1, U1401.76
LED_G: R2033.1, U1401.58
LED_R: R2032.1, U1401.57
LOOP_SENSE_A: R2006.2, U1401.83
LOOP_SENSE_B: R2012.2, U1401.84
MID_SENSE: J2302.26, R1407.1
NTC_BOARD1: J2302.28, R1412.2, R1413.1
NTC_BRAKE: J2302.29, R1418.2, R1419.1
NTC_EXHAUST: J2015.1, R1422.2, R1423.1
NTC_INTAKE: J2014.1, R1420.2, R1421.1
OUT_3V3_PERIPH: J2023.1, R1354.2, R1356.1, U1316.8
OUT_5V_PERIPH: J2022.1, R1350.2, R1352.1, U1314.8
OUT_7V4_SERVO: J2021.1, R1346.2, R1348.1, U1312.8
OUT_12V_AUX: J2019.1, R1330.2, R1332.1, U1308.8
OUT_12V_JETSON: J2017.1, R1314.2, R1316.1, U1304.8
OUT_12V_PI_STUB: J2020.1, R1338.2, R1340.1, U1310.8
OUT_12V_THIRD: J2018.1, R1322.2, R1324.1, U1306.8
OUT_24V: J2016.1, R1306.2, R1308.1, U1302.8
OUT_SPARE: J2024.1, R1362.2, R1364.1, U1318.8
PG_12V: R1110.1, R1440.1, U1102.10, U1401.15
PG_24V: R1121.1, R1441.1, U1103.10, U1401.16
PORT_EN1: J2301.15, U2032.18
PORT_EN2: J2301.16, U2032.16
PORT_EN3: J2301.17, U2032.14
PORT_EN4: J2301.18, U2032.12
PORT_EN5: J2301.19, U2032.9
PORT_EN6: J2301.20, U2032.7
PORT_REQ1: R2026.1, U1401.59, U2032.2
PORT_REQ2: R2027.1, U1401.60, U2032.4
PORT_REQ3: R2028.1, U1401.61, U2032.6
PORT_REQ4: R2029.1, U1401.62, U2032.8
PORT_REQ5: R2030.1, U1401.68, U2032.11
PORT_REQ6: R2031.1, U1401.80, U2032.13
POWER_BTN: D2006.1, J2010.5, R2036.1, U1401.8
QWIIC_SCL: J2013.4, R1435.1, U1402.10
QWIIC_SDA: J2013.3, R1434.1, U1402.9
RAIL_ALERT_A: R1373.1, U1302.3, U1304.3, U1306.3, U1308.3, U1310.3, U1401.19
RAIL_ALERT_B: R1374.1, U1312.3, U1314.3, U1316.3, U1318.3, U1320.3, U1401.20
RAIL_FLT: R1372.1, U1301.15, U1303.15, U1305.15, U1307.15, U1309.15, U1311.15, U1317.15, U1401.18
RAW_3V3: C1221.1, C1222.1, C1223.1, C1342.1, L1203.2, R1213.1, U1315.1, U1315.2
RAW_5V: C1214.1, C1215.1, C1337.1, C1531.1, C1601.1, C1602.1, C1651.1, C1652.1, C1701.1, C1702.1, C1751.1, C1752.1, C1801.1, C1802.1, C1851.1, C1852.1, D2007.1, L1202.2, LS2001.1, R1207.1, R1209.1, R1511.1, R1512.1, U1313.1, U1313.2, U1313.4, U1315.4, U1506.1, U1506.2, U1506.4, U1601.3, U1651.3, U1701.3, U1751.3, U1801.3, U1851.3
RAW_5V6: C1237.1, C1238.1, C1239.1, L1205.2, R1217.1, R1219.1, R1365.1, R1366.1, U1206.1
RAW_7V4: C1206.1, C1207.1, C1208.1, C1332.1, C1333.1, L1201.2, R1201.1, R1203.1, R1342.1, U1311.1, U1311.2, U1311.3, U1311.6
RAW_SPARE: C1229.1, C1230.1, C1231.1, C1348.1, C1349.1, L1204.2, R1215.1, R1358.1, U1317.1, U1317.2, U1317.3, U1317.6
SUP_OPEN_A: Q2001.1, R2005.1, U1401.81
SUP_OPEN_B: Q2002.1, R2011.1, U1401.82
TS2_WAKE: D2006.2, J2301.13
USB_A_DM: U1501.33, U1503.3
USB_A_DP: U1501.34, U1503.4
USB_B_DM: U1502.33, U1503.6
USB_B_DP: U1502.34, U1503.7
USB_SUP_DM: U1401.70, U1503.1
USB_SUP_DP: U1401.71, U1503.2
VMOT_SENSE: J2302.27, R1408.1
VSYS: C1101.1, C1150.1, C1151.1, C1152.1, C1153.1, J2301.1, J2301.2, J2301.3, J2301.4, J2301.5, J2301.6, Q1101.1, Q1101.2, Q1101.3, Q1105.5, R1119.1, R1409.1, U1101.1, U1101.4, U1103.20
WD_KICK: R2025.1, U1401.77, U2031.6
WD_N: R2016.1, R2018.1, U2031.7, U2031.8, U2033.2, U2034.2
WD_N_M: R2018.2, U1401.95
